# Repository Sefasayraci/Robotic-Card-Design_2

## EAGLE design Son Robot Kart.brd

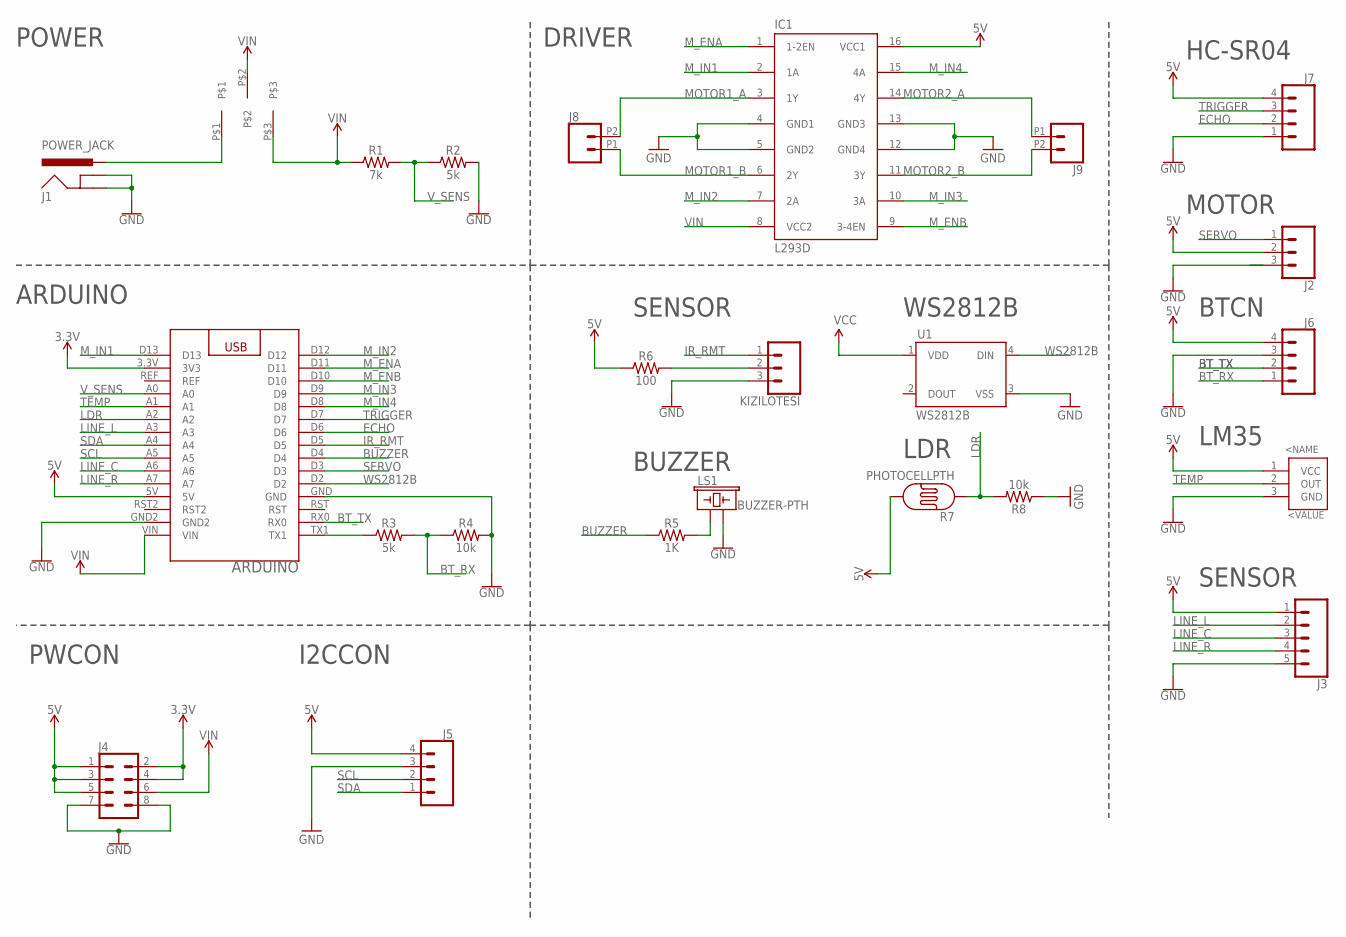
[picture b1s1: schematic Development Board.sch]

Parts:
ARDUINO: ARDUINONANO
IC1: L293D; DIL16
J1: POWER_JACK; POWER_JACK_PTH
J2: CONN_03; 1X03
J3: CONN_05; 1X05
J4: CONN_04X2; 2X4
J5, J6, J7: CONN_04; 1X04
J8, J9: CONN_022.54MM_SCREWTERM; 1X02_2.54_SCREWTERM
KIZILOTESI: CONN_03; 1X03
LM35: LM35; TO-92
LS1: BUZZER-PTH; BUZZER-12MM
R1: 7k; AXIAL-0.3
R2, R3: 5k; AXIAL-0.3
R4, R8: 10k; AXIAL-0.3
R5: 1K; AXIAL-0.3
R6: 100; AXIAL-0.3
R7: PHOTOCELLPTH; PHOTOCELL
SW1: SWITCH
U1: WS2812B

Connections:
3.3V: ARDUINO.3.3V (3V3), J4.2, J4.4
5V: ARDUINO.5V, IC1.16 (VCC1), J2.2, J3.1, J4.1, J4.3, J4.5, J5.4, J6.4, J7.4, LM35.1 (VCC), R6.P$1 (1), R7.2
BT_RX: J6.1, R3.P$2 (2), R4.P$1 (1)
BT_TX: ARDUINO.RX0, J6.2
BUZZER: ARDUINO.D4, R5.P$1 (1)
DO: J2.3
ECHO: ARDUINO.D6, J7.2
GND: ARDUINO.GND, ARDUINO.GND2, IC1.4 (GND1), IC1.5 (GND2), IC1.12 (GND4), IC1.13 (GND3), J1.GND, J1.GNDBREAK, J3.5, J4.7, J4.8, J5.3, J6.3, J7.1, KIZILOTESI.3, LM35.3 (GND), LS1.- (2), R2.P$2 (2), R4.P$2 (2), R8.P$1 (1), U1.3 (VSS)
IR_RMT: ARDUINO.D5, KIZILOTESI.1
LDR: ARDUINO.A2, R7.1, R8.P$2 (2)
LINE_C: ARDUINO.A6, J3.3
LINE_L: ARDUINO.A3, J3.2
LINE_R: ARDUINO.A7, J3.4
MOTOR1_A: IC1.3 (1Y), J8.P2 (2)
MOTOR1_B: IC1.6 (2Y), J8.P1 (1)
MOTOR2_A: IC1.14 (4Y), J9.P1 (1)
MOTOR2_B: IC1.11 (3Y), J9.P2 (2)
M_ENA: ARDUINO.D11, IC1.1 (1-2EN)
M_ENB: ARDUINO.D10, IC1.9 (3-4EN)
M_IN1: ARDUINO.D13, IC1.2 (1A)
M_IN2: ARDUINO.D12, IC1.7 (2A)
M_IN3: ARDUINO.D9, IC1.10 (3A)
M_IN4: ARDUINO.D8, IC1.15 (4A)
unnamed: ARDUINO.TX1, R3.P$1 (1)
unnamed: LS1.+ (1), R5.P$2 (2)
unnamed: J1.PWR, SW1.P$1
unnamed: KIZILOTESI.2, R6.P$2 (2)
SCL: ARDUINO.A5, J5.2
SDA: ARDUINO.A4, J5.1
SERVO: ARDUINO.D3, J2.1
TEMP: ARDUINO.A1, LM35.2 (OUT)
TRIGGER: ARDUINO.D7, J7.3
VCC: U1.1 (VDD)
VIN: ARDUINO.VIN, IC1.8 (VCC2), J4.6, R1.P$1 (1), SW1.P$2, SW1.P$3
V_SENS: ARDUINO.A0, R1.P$2 (2), R2.P$1 (1)
WS2812B: ARDUINO.D2, U1.4 (DIN)

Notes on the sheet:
POWER
ARDUINO
DRIVER
SENSOR
BUZZER
LM35
MOTOR
BTCN
HC-SR04
LDR
PWCON
I2CCON
WS2812B

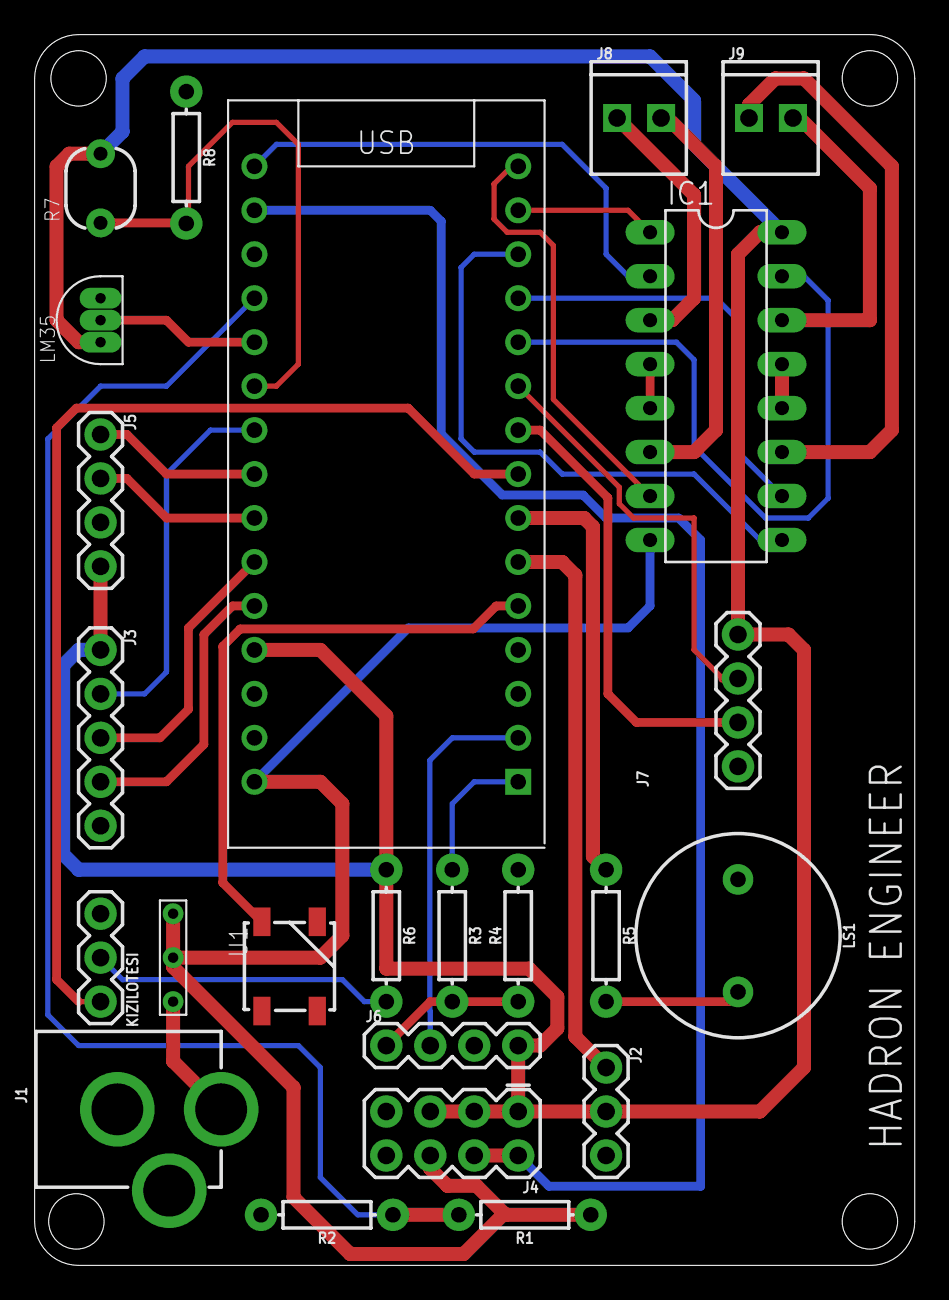
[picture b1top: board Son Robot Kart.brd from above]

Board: 2 copper layers, 50.9 x 71.1 mm, 24 parts (0 on the bottom side), 34 nets.

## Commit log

2021-04-03 Robotic Card Design_2

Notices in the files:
parts and their libraries:
SparkFun-Resistors: Licensing: Creative Commons ShareAlike 4.0 International - https://creativecommons.org/licenses/by-sa/4.0
SparkFun-LED: Licensing: CC v3.0 Share-Alike You are welcome to use this library for commercial purposes.
